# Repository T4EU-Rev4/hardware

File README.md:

# hardware
Collection of the hardware items used in the train project
All schematics and pcbs are made with KiCAD https://www.kicad.org/ 

## Node
Here are the schematic and the pcb files of a small controller board located. This board can be used as a I2C client but also supports RS485 if necessary.

## Node_MP3
This folder contains the schematic and the software for the wagon DK MP3, witch contains a small mp3 player.

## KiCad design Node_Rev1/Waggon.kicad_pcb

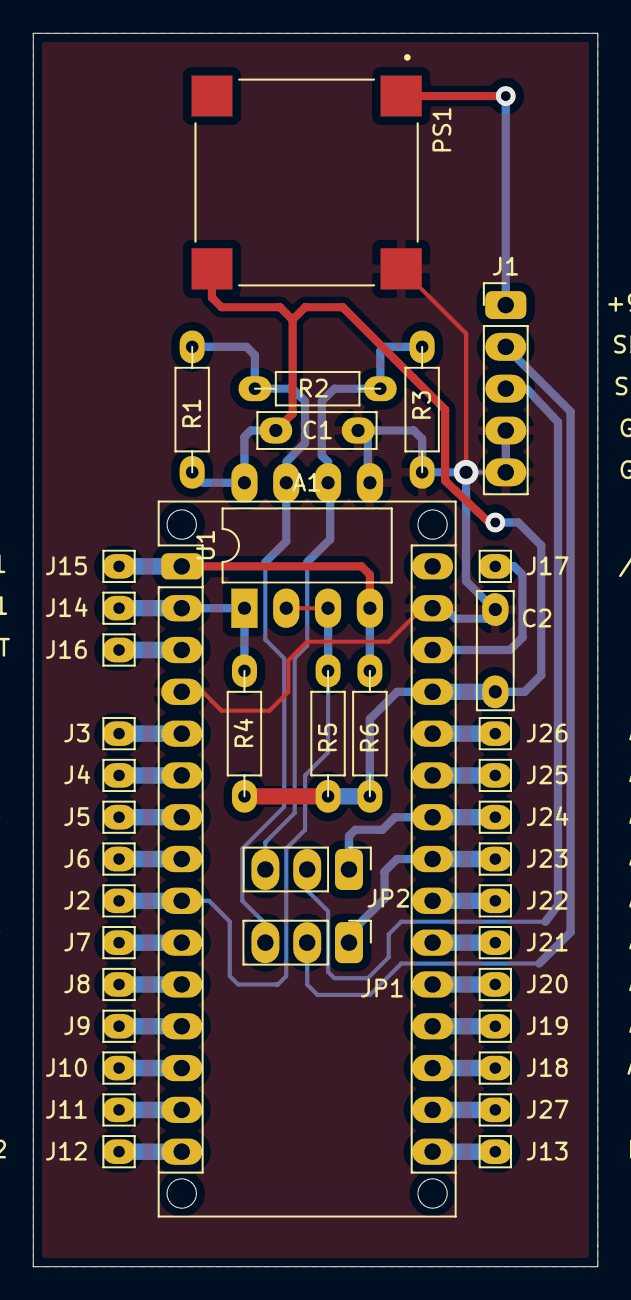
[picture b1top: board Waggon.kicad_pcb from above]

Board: 2 copper layers, 34.3 x 74.9 mm, 40 parts (0 on the bottom side), 33 nets.

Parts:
A1: Arduino_Nano_Every; Arduino_Nano_WithMountingHoles
C1, C2: 100n; C_Rect_L7.0mm_W2.0mm_P5.00mm
J1: Screw_Terminal_01x05; PinHeader_1x05_P2.54mm_Vertical
J2, J3, J4, J5, J6, J7, J8, J9, J10, J11, J12, J13, J14, J15, J16, J17, J18, J19, J20, J21, J22, J23, J24, J25, J26, J27: Conn_01x01; TestPoint_THTPad_1.5x1.5mm_Drill0.7mm
JP1, JP2: Jumper_3_Bridged12; PinHeader_1x03_P2.54mm_Vertical
PS1: ROF-78E5.0-0.5SMD-R; CONV_ROF-78E5.0-0.5SMD-R
R1, R3: 680R; R_7.5
R2: 120R; R_7.5
R4, R5, R6: 10k; R_7.5
U1: MAX485E; DIP-8_W7.62mm_LongPads

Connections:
GND: A1.4 (GND), A1.29 (GND), C1.2, C2.1, J1.4, J1.5, PS1.2 (GND), R3.2, U1.5 (GND)
unnamed: A1.1 (TX1), J15.1, R6.2, U1.4 (DI)
unnamed: A1.2 (RX1), J14.1, R4.2, U1.1 (RO)
unnamed: A1.3 (~RESET), J16.1
unnamed: A1.5 (D2), J3.1
unnamed: A1.6 (D3), J4.1
unnamed: A1.7 (D4), J5.1
unnamed: A1.8 (D5), J6.1
unnamed: A1.9 (D6), J2.1, R5.2, U1.2 (~RE), U1.3 (DE)
unnamed: A1.10 (D7), J7.1
unnamed: A1.11 (D8), J8.1
unnamed: A1.12 (D9), J9.1
unnamed: A1.13 (D10), J10.1
unnamed: A1.14 (MOSI), J11.1
unnamed: A1.15 (MISO), J12.1
unnamed: A1.16 (SCK), J13.1
unnamed: A1.17 (3V3), J27.1
unnamed: A1.18 (AREF), J18.1
unnamed: A1.19 (A0), J19.1
unnamed: A1.20 (A1), J20.1
unnamed: A1.21 (A2), J21.1
unnamed: A1.22 (A3), J22.1
unnamed: A1.23 (SDA/A4), J23.1, JP1.1 (A)
unnamed: A1.24 (SCL/A5), J24.1, JP2.1 (A)
unnamed: A1.25 (A6), J25.1
unnamed: A1.26 (A7), J26.1
unnamed: A1.27 (+5V), C1.1, C2.2, PS1.3 (+VOUT), R1.1, R4.1, R5.1, R6.1, U1.8 (VCC)
unnamed: A1.28 (~RESET), J17.1
unnamed: J1.1, PS1.1 (+VIN)
unnamed: J1.2, JP1.2 (C)
unnamed: J1.3, JP2.2 (C)
unnamed: JP1.3 (B), R1.2, R2.1, U1.7 (B)
unnamed: JP2.3 (B), R2.2, R3.1, U1.6 (A)

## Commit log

2022-07-24 This is the first version of a board capable to emulate the PCF8575 as well as communicate via RS485 to support a ModBus-Server oder ModBus-Client for example.
2022-07-25 Adding KiCAD Footprints
2022-08-27 Schematic of Node-MP3
2022-09-25 Updating Descriptions
2022-10-09 Rev2 of the board completed an send to manufacturer
2022-10-09 typos corrected
2022-11-09 Node Rev.2: DC-DC-Converter replaced by one with a smaller footprint
2022-11-09 Test with EMQX as public broker to see, if more than one topis are possible
2022-11-23 Schematic ESP32 at the loco V0.1
2023-05-06 - Link to GitHub added - Schematic as PDf created
